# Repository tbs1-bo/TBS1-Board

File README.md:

# TBS1-Board

Das "TBS1-Board" ist ein Übungsboard zur Programmierung von Mikrocontrollern. Es wurde 2017 im Rahmen eines Projektes der Fachschule für Technik an der Technischen Beruflichen Schule 1 in Bochum (TBS1) entwickelt. Das Übungsboard kommt bei der Technikerausbildung zum Einsatz.

## TBS1-Board 2017

- [Projektdokumentation (Auszug)](Projektdokumentation_2017_Auszug.pdf)
- [Schaltung und Platinenlayout](Schaltung_und_Platinenlayout)

## Weiterentwicklung

Infos folgen ...

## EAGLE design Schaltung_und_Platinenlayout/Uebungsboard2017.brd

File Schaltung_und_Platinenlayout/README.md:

# TBS1-Board / Schaltung und Platinenlayout (Stand: 2017)

- [Stückliste](Stueckliste_2017.pdf)

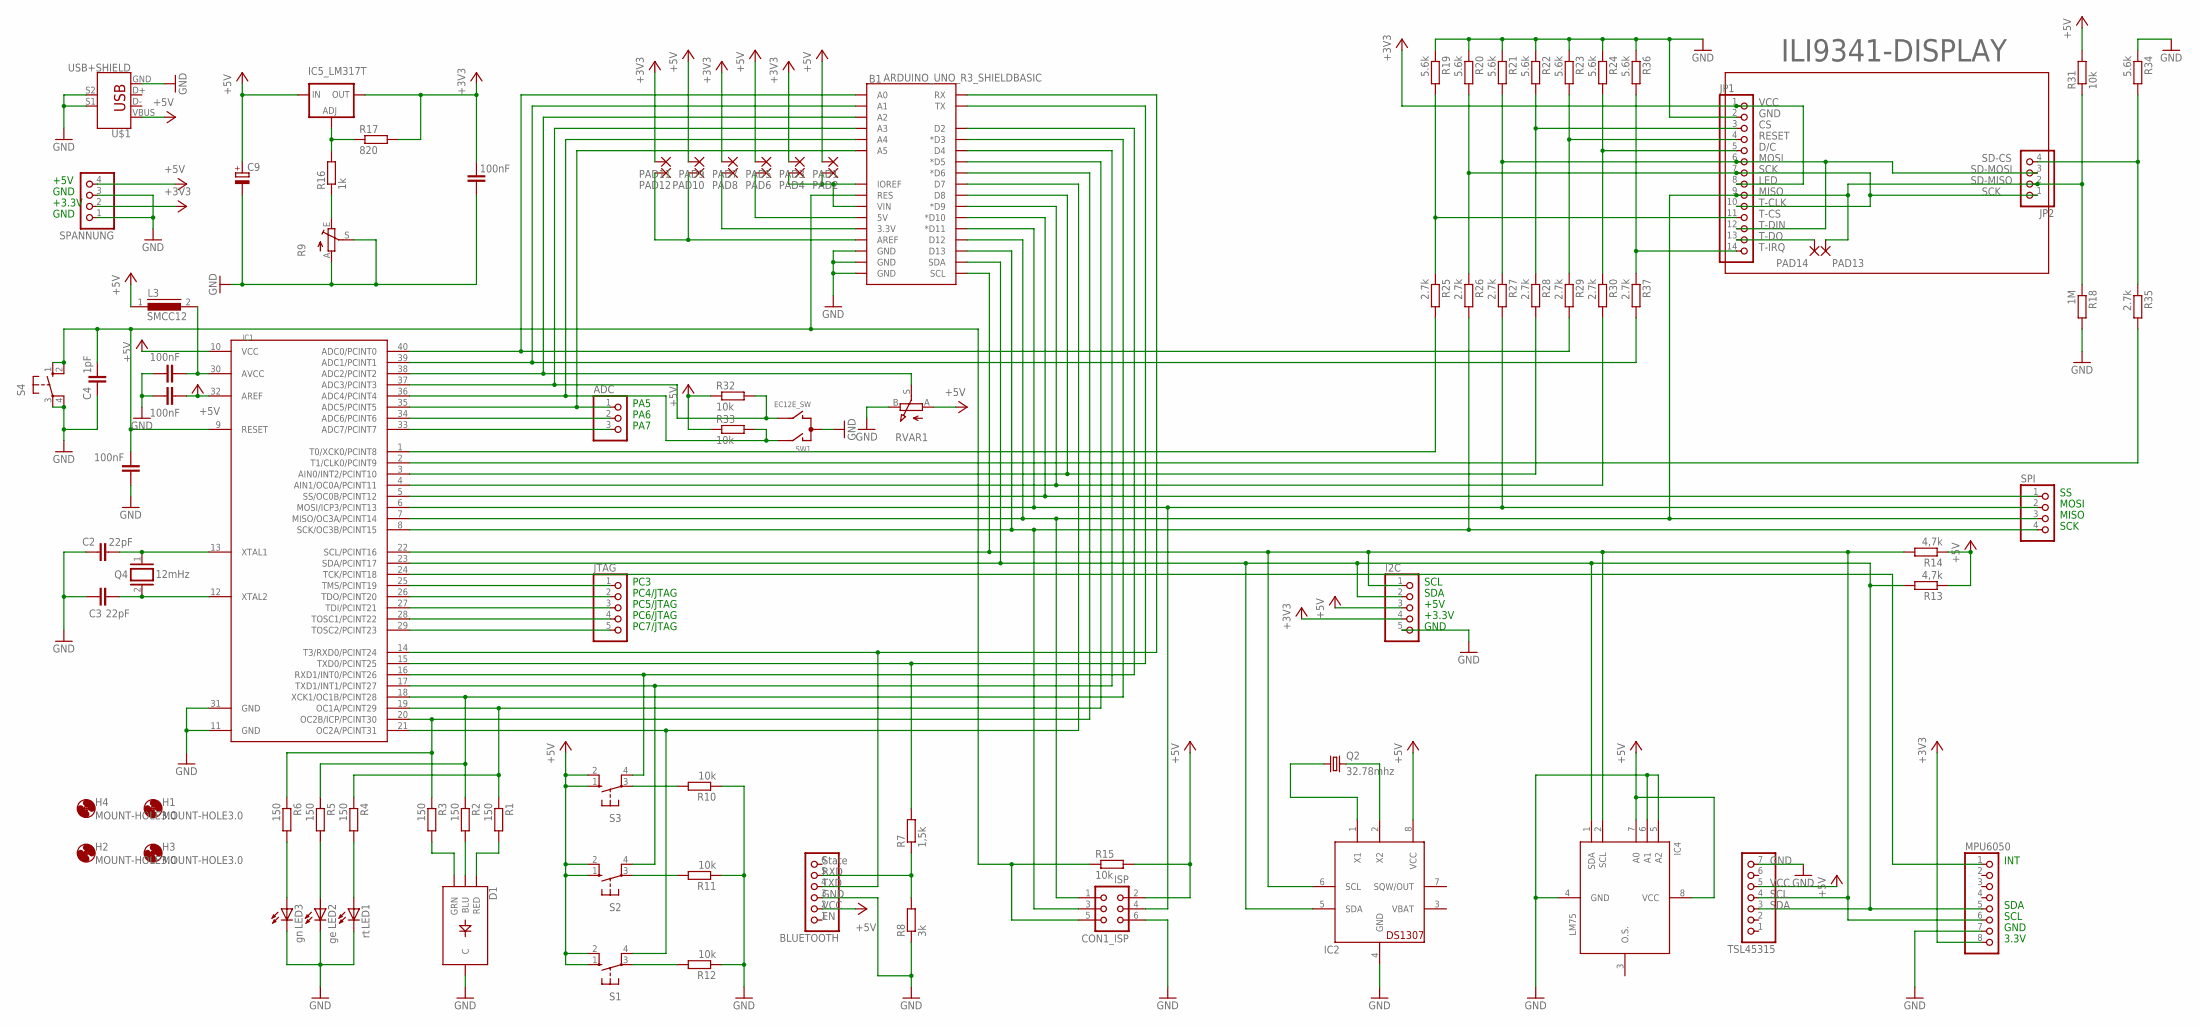
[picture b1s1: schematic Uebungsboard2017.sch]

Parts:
ADC: PINHD-1X3; 1X03
B1: ARDUINO_UNO_R3_SHIELDBASIC; UNO_R3_SHIELD
BLUETOOTH: PINHD-1X6; 1X06
C2, C3: 22pF; C5B2.5
C4: 1pF; C5B2.5
C5, C6, C7, C8: 100nF; C5B2.5
C9: CPOL-EUE2-5; E2-5
CON1_ISP: ISP; CON06
D1: LED-RGB-CCTEST; LED-RGB-THRU
H1, H2, H3, H4: MOUNT-HOLE3.0; 3,0
I2C: PINHD-1X5; 1X05
IC1: MEGA1284P; DIL40
IC2: DS1307; DIL08
IC4: DS1721S; SO-8
IC5_LM317T: 3.3V; 317TS
JP1: PINHD-1X14; 1X14
JP2: PINHD-1X4; 1X04
JTAG: PINHD-1X5; 1X05
L3: SMCC12
LED1: rt; LED5MM
LED2: ge; LED5MM
LED3: gn; LED5MM
MPU6050: PINHD-1X8; 1X08
PAD1, PAD2, PAD3, PAD4, PAD5, PAD6, PAD7, PAD8, PAD9, PAD10, PAD11, PAD12, PAD13, PAD14: 1,6/0,8
Q2: 32.78mhz; TC26H
Q4: 12mHz; QS
R1, R2, R3, R4, R5, R6: 150; 0207/10
R7: 1,5k; 0207/10
R8: 3k; 0207/10
R9: TRIM_EU-S63P; S63P
R10, R11, R12, R15, R31, R32, R33: 10k; 0207/10
R13, R14: 4,7k; 0207/10
R16: 1k; 0207/10
R17: 820; 0207/10
R18: 1M; 0207/10
R19, R20, R21, R22, R23, R24, R34, R36: 5.6k; 0207/10
R25, R26, R27, R28, R29, R30, R35, R37: 2.7k; 0207/10
RVAR1: RK09K113
S1, S2, S3, S4: 10-XX; B3F-10XX
SPANNUNG: PINHD-1X4; 1X04
SPI: PINHD-1X4; 1X04
SW1: EC12E_SW; ALPS_EC12E_SW
TSL45315: PINHD-1X7; 1X07
U$1: USB+SHIELD; USB-B-PTH

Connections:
+3V3: C5.1, I2C.4, IC5_LM317T.2 (OUT), JP1.1, JP1.8, MPU6050.8, PAD3.1, PAD7.1, PAD11.1, R17.2, SPANNUNG.2
+5V: BLUETOOTH.2, C6.1, C9.+, CON1_ISP.2, I2C.3, IC1.10 (VCC), IC1.32 (AREF), IC2.8 (VCC), IC4.7 (A0), IC4.8 (VCC), IC5_LM317T.3 (IN), L3.1, PAD1.1, PAD5.1, PAD9.1, R13.1, R14.1, R15.2, R31.2, R32.1, R33.1, RVAR1.A, S1.1 (S), S1.2 (S1), S2.1 (S), S2.2 (S1), S3.1 (S), S3.2 (S1), SPANNUNG.4, TSL45315.5, U$1.VBUS
GND: B1.GND@0 (GND), B1.GND@1 (GND), B1.GND@2 (GND), BLUETOOTH.3, C2.2, C3.1, C4.2, C5.2, C6.2, C7.2, C8.2, C9.-, CON1_ISP.6, D1.2 (C), I2C.5, IC1.11 (GND), IC1.31 (GND), IC2.4 (GND), IC4.4 (GND), IC4.5 (A2), IC4.6 (A1), JP1.2, LED1.K (C), LED2.K (C), LED3.K (C), MPU6050.7, R8.1, R9.A, R9.S, R10.1, R11.1, R12.1, R18.2, R19.1, R20.1, R21.1, R22.1, R23.1, R24.1, R34.1, R36.1, RVAR1.B (E), S4.3, S4.4 (P1), SPANNUNG.1, SPANNUNG.3, SW1.C, TSL45315.7, U$1.GND, U$1.S1, U$1.S2
unnamed: B1.D5 (*D5), IC1.19 (OC1A/PCINT29), R1.1, R4.1
unnamed: C2.1, IC1.13 (XTAL1), Q4.1
unnamed: B1.D3 (*D3), IC1.18 (XCK1/OC1B/PCINT28), R2.1, R5.1
unnamed: C3.2, IC1.12 (XTAL2), Q4.2
unnamed: B1.D6 (*D6), IC1.20 (OC2B/ICP/PCINT30), R3.1, R6.1
unnamed: D1.1 (RED), R1.2
unnamed: D1.4 (BLU), R2.2
unnamed: D1.3 (GRN), R3.2
unnamed: LED1.A, R4.2
unnamed: LED2.A, R5.2
unnamed: LED3.A, R6.2
unnamed: B1.D12, CON1_ISP.1, IC1.7 (MISO/OC3A/PCINT14), JP1.9, JP2.2, PAD13.1, R18.1, R31.1, SPI.3
unnamed: ADC.1, B1.A5, IC1.35 (ADC5/PCINT5)
unnamed: IC2.2 (X2), Q2.2
unnamed: B1.D11 (*D11), CON1_ISP.4, IC1.6 (MOSI/ICP3/PCINT13), R27.2, SPI.2
unnamed: B1.A1, IC1.39 (ADC1/PCINT1), R37.2
unnamed: IC1.24 (TCK/PCINT18), MPU6050.1
unnamed: B1.A2, IC1.38 (ADC2/PCINT2), RVAR1.S
unnamed: IC5_LM317T.1 (ADJ), R16.2, R17.1
unnamed: IC2.1 (X1), Q2.1
unnamed: B1.RX, BLUETOOTH.4, IC1.14 (T3/RXD0/PCINT24)
unnamed: BLUETOOTH.5, R7.1, R8.2
unnamed: B1.SCL, I2C.1, IC1.22 (SCL/PCINT16), IC2.6 (SCL), IC4.2 (SCL), MPU6050.6, R14.2, TSL45315.4
unnamed: B1.D4, IC1.17 (TXD1/INT1/PCINT27), S2.4 (P1)
unnamed: B1.D2, IC1.16 (RXD1/INT0/PCINT26), S3.4 (P1)
unnamed: R10.2, S3.3
unnamed: R11.2, S2.3
unnamed: R12.2, S1.3
unnamed: C7.1, IC1.30 (AVCC), L3.2
unnamed: B1.TX, IC1.15 (TXD0/PCINT25), R7.2
unnamed: JP1.11, R19.2, R25.1
unnamed: IC1.25 (TMS/PCINT19), JTAG.1
unnamed: R9.E, R16.1
unnamed: JP1.7, JP1.10, JP2.1, R20.2, R26.1
unnamed: JP1.6, JP1.12, JP2.3, R21.2, R27.1
unnamed: JP1.3, R22.2, R28.1
unnamed: JP1.4, R23.2, R29.1
unnamed: JP1.5, R24.2, R30.1
unnamed: B1.A4, IC1.36 (ADC4/PCINT4), R33.2, SW1.A
unnamed: IC1.1 (T0/XCK0/PCINT8), R25.2
unnamed: B1.D8, IC1.3 (AIN0/INT2/PCINT10), R28.2
unnamed: B1.A0, IC1.40 (ADC0/PCINT0), R29.2
unnamed: B1.D9 (*D9), IC1.4 (AIN1/OC0A/PCINT11), R30.2
unnamed: B1.A3, IC1.37 (ADC3/PCINT3), R32.2, SW1.B
unnamed: JP2.4, R34.2, R35.1
unnamed: IC1.2 (T1/CLK0/PCINT9), R35.2
unnamed: IC1.26 (TDO/PCINT20), JTAG.2
unnamed: IC1.27 (TDI/PCINT21), JTAG.3
unnamed: IC1.28 (TOSC1/PCINT22), JTAG.4
unnamed: B1.D13, CON1_ISP.3, IC1.8 (SCK/OC3B/PCINT15), R26.2, SPI.4
unnamed: B1.D10 (*D10), IC1.5 (SS/OC0B/PCINT12), SPI.1
unnamed: B1.D7, IC1.21 (OC2A/PCINT31), S1.4 (P1)
unnamed: IC1.29 (TOSC2/PCINT23), JTAG.5
unnamed: B1.IOREF, B1.VIN, PAD2.1, PAD4.1
unnamed: B1.5V, PAD6.1
unnamed: B1.3.3V, PAD8.1
unnamed: B1.AREF, PAD10.1, PAD12.1
unnamed: ADC.2, IC1.34 (ADC6/PCINT6)
unnamed: ADC.3, IC1.33 (ADC7/PCINT7)
unnamed: JP1.13, PAD14.1
unnamed: B1.RES, C4.1, C8.1, CON1_ISP.5, IC1.9 (RESET), R15.1, S4.1 (S), S4.2 (S1)
unnamed: JP1.14, R36.2, R37.1
unnamed: B1.SDA, I2C.2, IC1.23 (SDA/PCINT17), IC2.5 (SDA), IC4.1 (SDA), MPU6050.5, R13.2, TSL45315.3
VBAT: IC2.3 (VBAT)

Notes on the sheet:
State
RXD
TXD
GND
VCC
SDA
SCL
ILI9341-DISPLAY
RESET
D/C
MOSI
SCK
LED
MISO
T-CLK
T-CS
T-DIN
T-DO
T-IRQ
SD-CS
SD-MOSI
SD-MISO
+5V
+3.3V
PA5
PA6
PA7
PC7/JTAG
PC6/JTAG
PC5/JTAG
PC4/JTAG
PC3
INT
3.3V

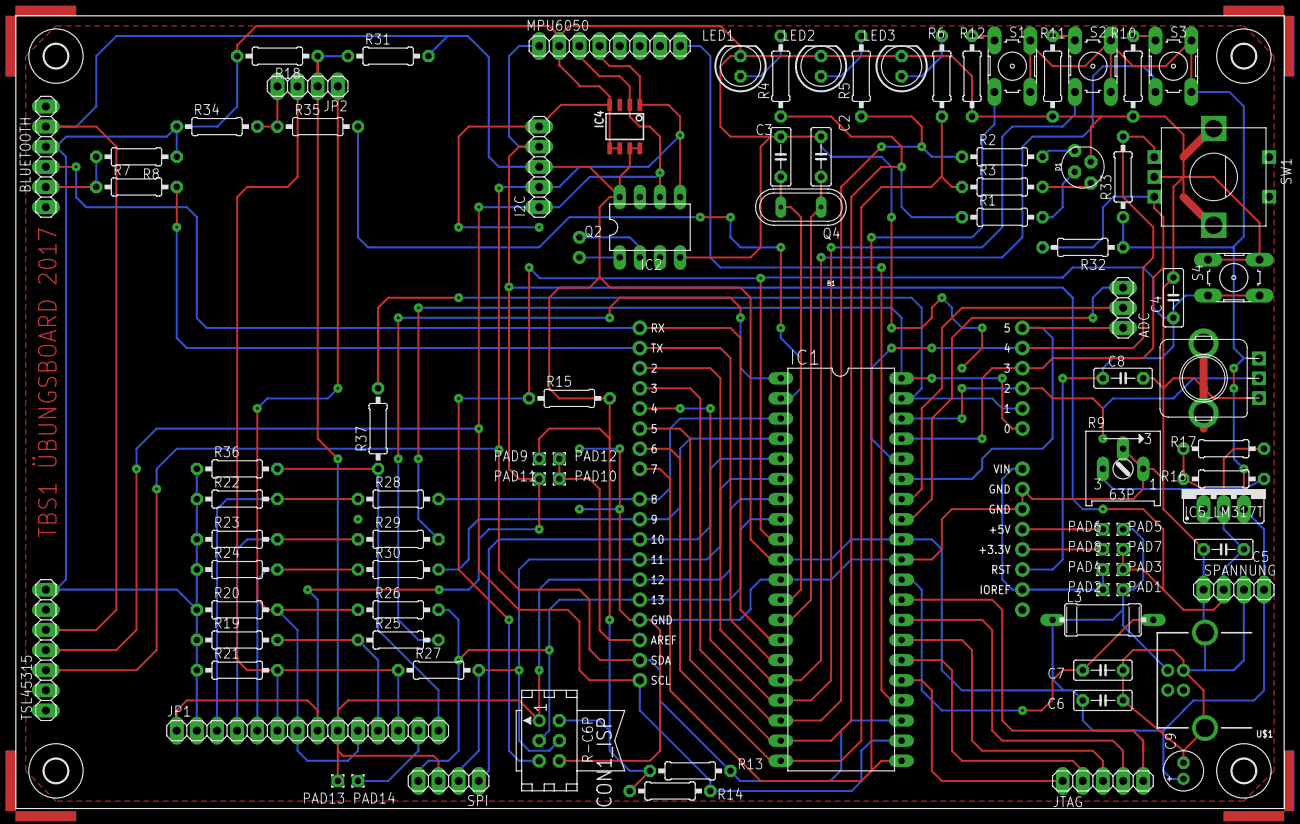
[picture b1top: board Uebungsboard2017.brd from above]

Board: 2 copper layers, 160.0 x 100.0 mm, 101 parts (1 on the bottom side), 66 nets.

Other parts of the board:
U$2, U$3, U$4, U$5: ANGLE-ARROW-NW1
U$6, U$7, U$8, U$9: ANGLE-ARROW-NW1-16

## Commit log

2019-03-21 Schaltung und Layout (TBS1-Board 2017) hinzugefügt
2019-03-21 Dokumentation hinzugefügt
2019-03-21 kleine Änderung
2019-03-21 keine Leerzeichen
2019-03-22 Stückliste hinzugefügt

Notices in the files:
parts and their libraries:
SparkFun-Retired: Licensing: Creative Commons ShareAlike 4.0 International - https://creativecommons.org/licenses/by-sa/4.0
